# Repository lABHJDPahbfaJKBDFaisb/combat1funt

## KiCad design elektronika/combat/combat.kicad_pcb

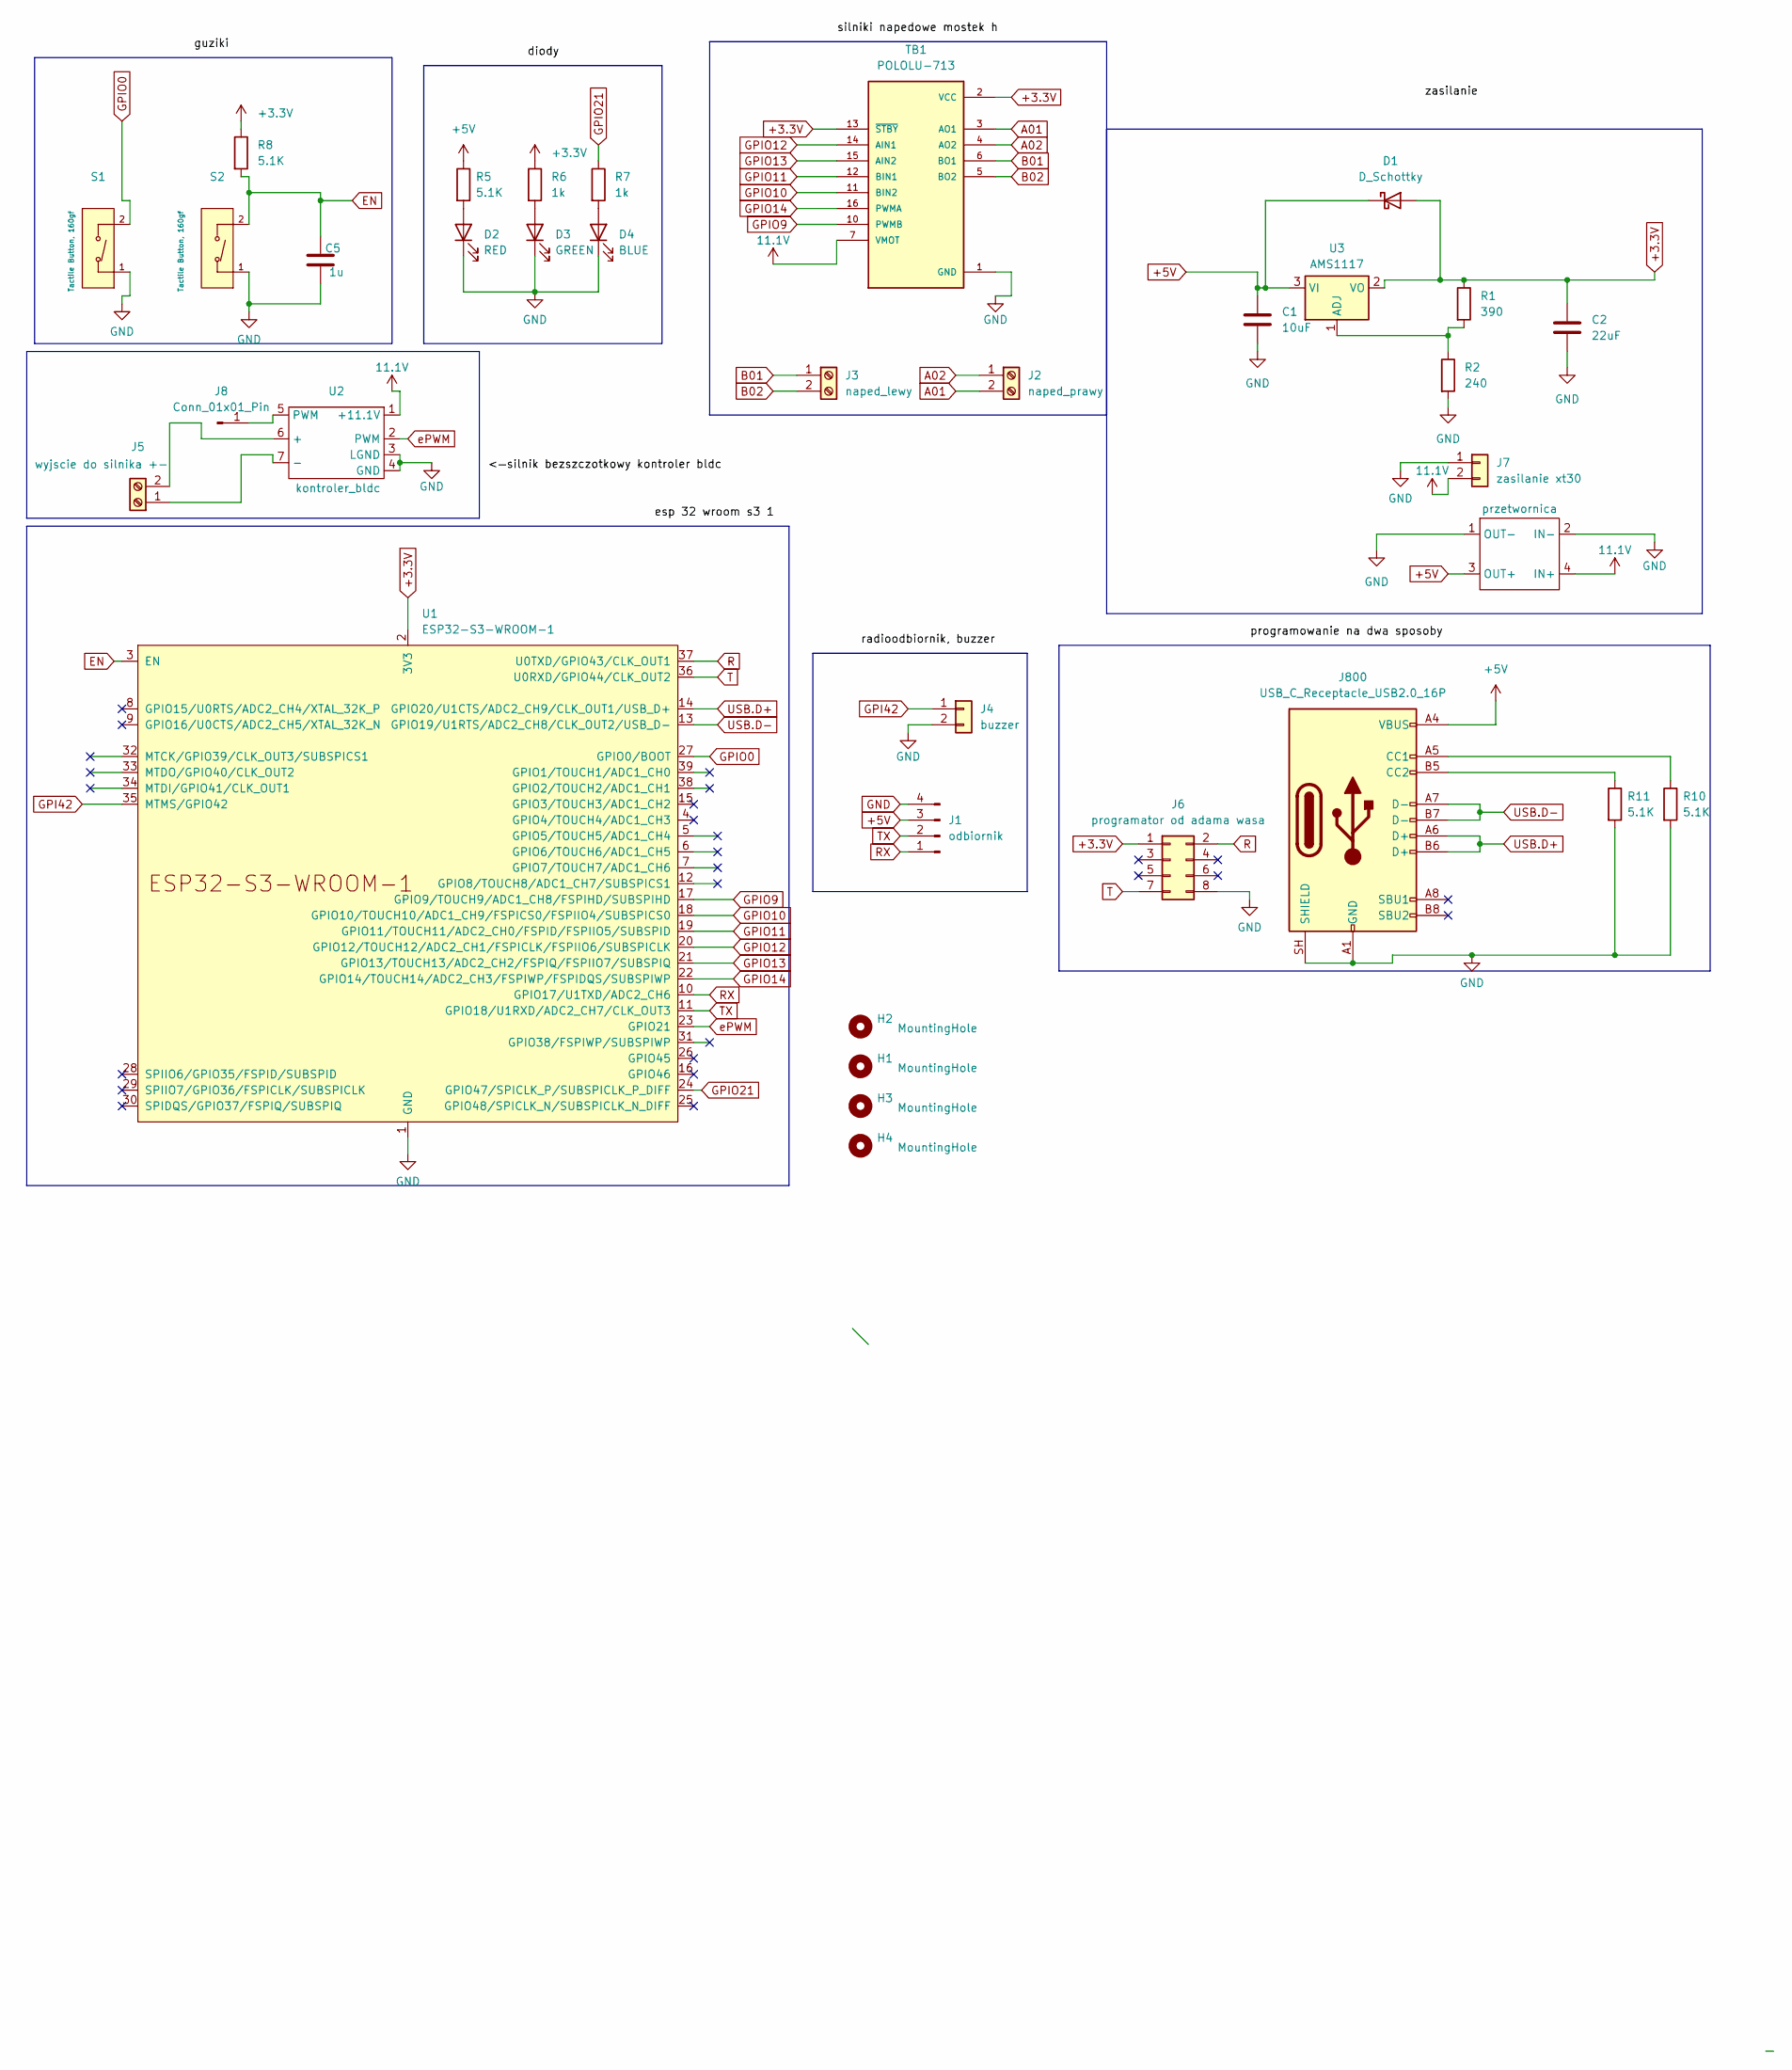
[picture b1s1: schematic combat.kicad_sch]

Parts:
C1: 10uF; C_0603_1608Metric_Pad1.08x0.95mm_HandSolder
C2: 22uF; C_1210_3225Metric_Pad1.33x2.70mm_HandSolder
C5: 1u; C_0603_1608Metric
D1: D_Schottky; D_DO-41_SOD81_P10.16mm_Horizontal
D2: RED; LED_0603_1608Metric
D3: GREEN; LED_0603_1608Metric
D4: BLUE; LED_0603_1608Metric
H1, H2, H3, H4: MountingHole; MountingHole_3.2mm_M3_Pad_Via
J1: odbiornik; PinHeader_1x04_P2.54mm_Vertical
J2: naped_prawy; AMASS_XT30U-F_1x02_P5.0mm_Vertical
J3: naped_lewy; AMASS_XT30U-F_1x02_P5.0mm_Vertical
J4: buzzer; PinSocket_1x02_P2.54mm_Vertical
J5: wyjscie do silnika +-; AMASS_XT30U-F_1x02_P5.0mm_Vertical
J6: programator od adama wasa; PinHeader_2x04_P2.54mm_Vertical
J7: zasilanie xt30; AMASS_XT30U-F_1x02_P5.0mm_Vertical
J8: Conn_01x01_Pin; PinHeader_1x01_P2.54mm_Vertical
J800: USB_C_Receptacle_USB2.0_16P; USB_C_Receptacle_GCT_USB4105-xx-A_16P_TopMnt_Horizontal; LCSC C165948
R1: 390; R_0603_1608Metric
R2: 240; R_0603_1608Metric
R5, R8, R10, R11: 5.1K; R_0603_1608Metric
R6, R7: 1k; R_0603_1608Metric
S1, S2: Tactile Button, 160gf; SW_TS-1088-AR02016; Voltage Rating (Dc) 12V; Part TS-1088-AR02016; LCSC C720477
TB1: POLOLU-713; SHIELD_POLOLU-713
U1: ESP32-S3-WROOM-1
U2: kontroler_bldc; BLDC
U3: AMS1117; SOT-223-3_TabPin2
U4: przetwornica; Bez_nazwy

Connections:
11.1V: J7.2, TB1.7 (VMOT), U2.1 (+11.1V), U4.4 (IN+)
+3.3V: C2.2, D1.2 (A), J6.1, R1.1, R6.1, R8.1, TB1.2 (VCC), TB1.13 (~STBY), U1.2 (3V3), U3.2 (VO)
+5V: C1.1, D1.1 (K), J1.3, J800.A4 (VBUS), J800.A9 (VBUS), J800.B4 (VBUS), J800.B9 (VBUS), R5.1, U3.3 (VI), U4.3 (OUT+)
A01: J2.2, TB1.3 (AO1)
A02: J2.1, TB1.4 (AO2)
B01: J3.1, TB1.6 (BO1)
B02: J3.2, TB1.5 (BO2)
EN: C5.1, R8.2, S2.2 (B), U1.3 (EN)
GND: C1.2, C2.1, C5.2, D2.1 (K), D3.1 (K), D4.1 (K), J1.4, J4.2, J6.8, J7.1, J800.A1 (GND), J800.A12 (GND), J800.B1 (GND), J800.B12 (GND), J800.SH (SHIELD), R2.2, R10.2, R11.2, S1.1 (A), S2.1 (A), TB1.1 (GND), TB1.8 (GND), TB1.9 (GND), U1.1 (GND), U1.40 (GND), U1.41 (GND), U2.3 (LGND), U2.4 (GND), U4.1 (OUT-), U4.2 (IN-)
GPI42: J4.1, U1.35 (MTMS/GPIO42)
GPIO0: S1.2 (B), U1.27 (GPIO0/BOOT)
GPIO9: TB1.10 (PWMB), U1.17 (GPIO9/TOUCH9/ADC1_CH8/FSPIHD/SUBSPIHD)
GPIO10: TB1.11 (BIN2), U1.18 (GPIO10/TOUCH10/ADC1_CH9/FSPICS0/FSPIIO4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)
GPIO11: TB1.12 (BIN1), U1.19 (GPIO11/TOUCH11/ADC2_CH0/FSPID/FSPIIO5/S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)
GPIO12: TB1.14 (AIN1), U1.20 (GPIO12/TOUCH12/ADC2_CH1/FSPICLK/FSPIIO6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)
GPIO13: TB1.15 (AIN2), U1.21 (GPIO13/TOUCH13/ADC2_CH2/FSPIQ/FSPIIO7/S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)
GPIO14: TB1.16 (PWMA), U1.22 (GPIO14/TOUCH14/ADC2_CH3/FSPIWP/FSPIDQS/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)
GPIO21: R7.1, U1.24 (GPIO47/SPICLK_P/SUBSPICLK_P_DIFF)
unnamed: D2.2 (A), R5.2
unnamed: D3.2 (A), R6.2
unnamed: D4.2 (A), R7.2
unnamed: J5.1, U2.7 (-)
unnamed: J5.2, U2.6 (+)
unnamed: J8.1 (Pin_1_1), U2.5 (PWM)
unnamed: J800.A5 (CC1), R10.1
unnamed: J800.B5 (CC2), R11.1
unnamed: R1.2, R2.1, U3.1 (ADJ)
R: J6.2, U1.37 (U0TXD/GPIO43/CLK_OUT1)
RX: J1.1, U1.10 (GPIO17/U1TXD/ADC2_CH6)
T: J6.7, U1.36 (U0RXD/GPIO44/CLK_OUT2)
TX: J1.2, U1.11 (GPIO18/U1RXD/ADC2_CH7/CLK_OUT3)
USB.D+: J800.A6 (D+), J800.B6 (D+), U1.14 (GPIO20/U1CTS/ADC2_CH9/CLK_OUT1/USB_D+)
USB.D-: J800.A7 (D-), J800.B7 (D-), U1.13 (GPIO19/U1RTS/ADC2_CH8/CLK_OUT2/USB_D-)
ePWM: U1.23 (GPIO21), U2.2 (PWM)

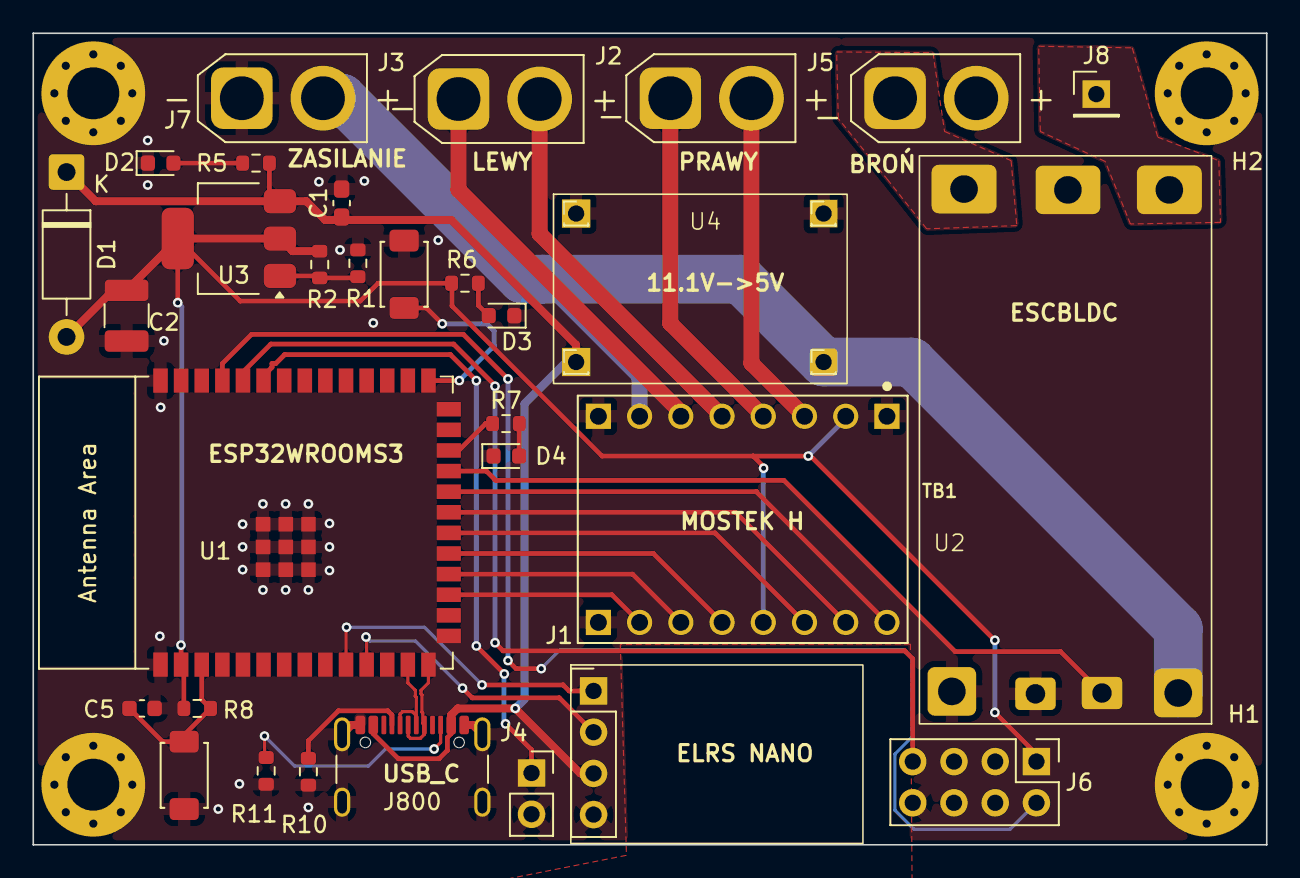
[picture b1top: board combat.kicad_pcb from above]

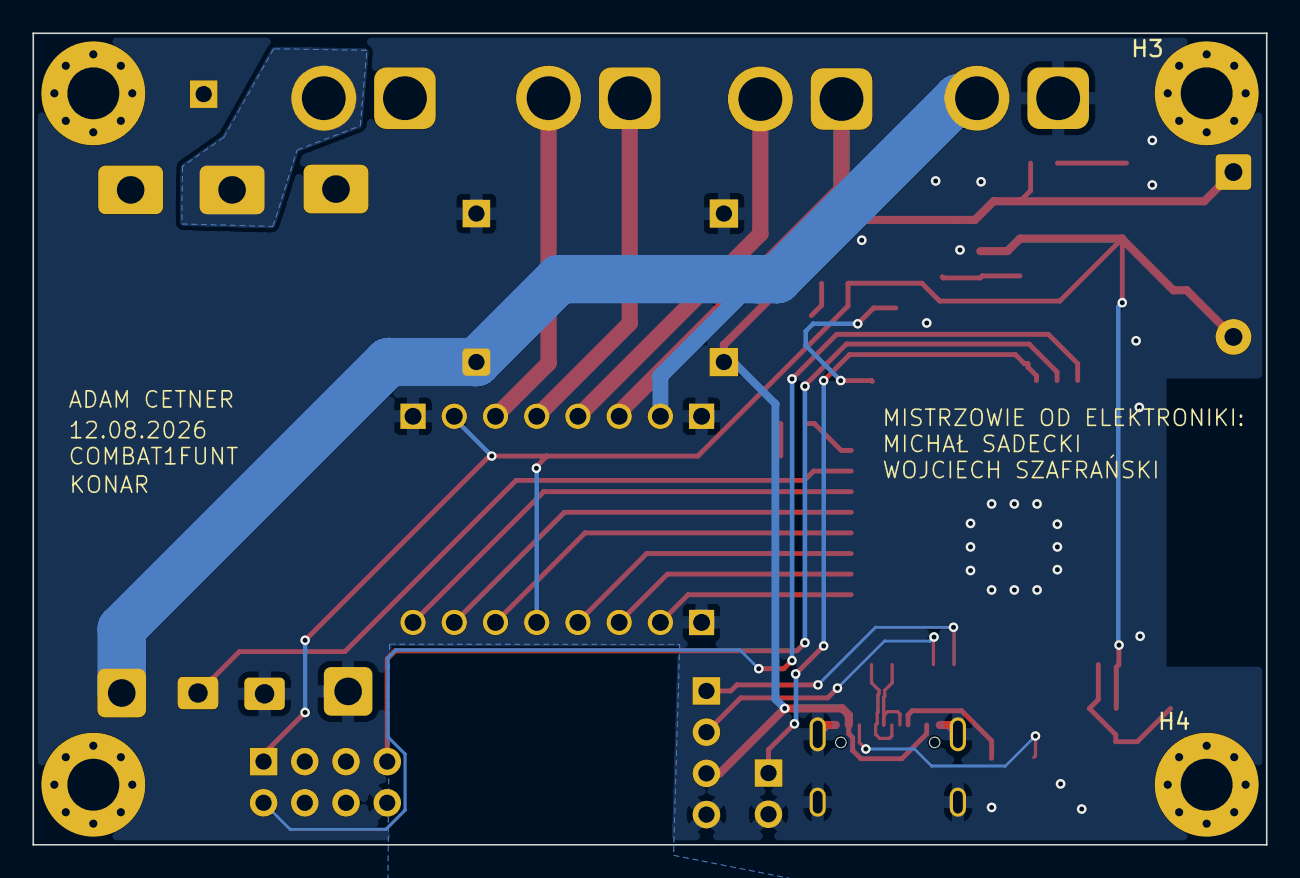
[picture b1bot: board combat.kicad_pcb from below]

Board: 2 copper layers, 76.0 x 50.0 mm, 35 parts (2 on the bottom side), 34 nets.
